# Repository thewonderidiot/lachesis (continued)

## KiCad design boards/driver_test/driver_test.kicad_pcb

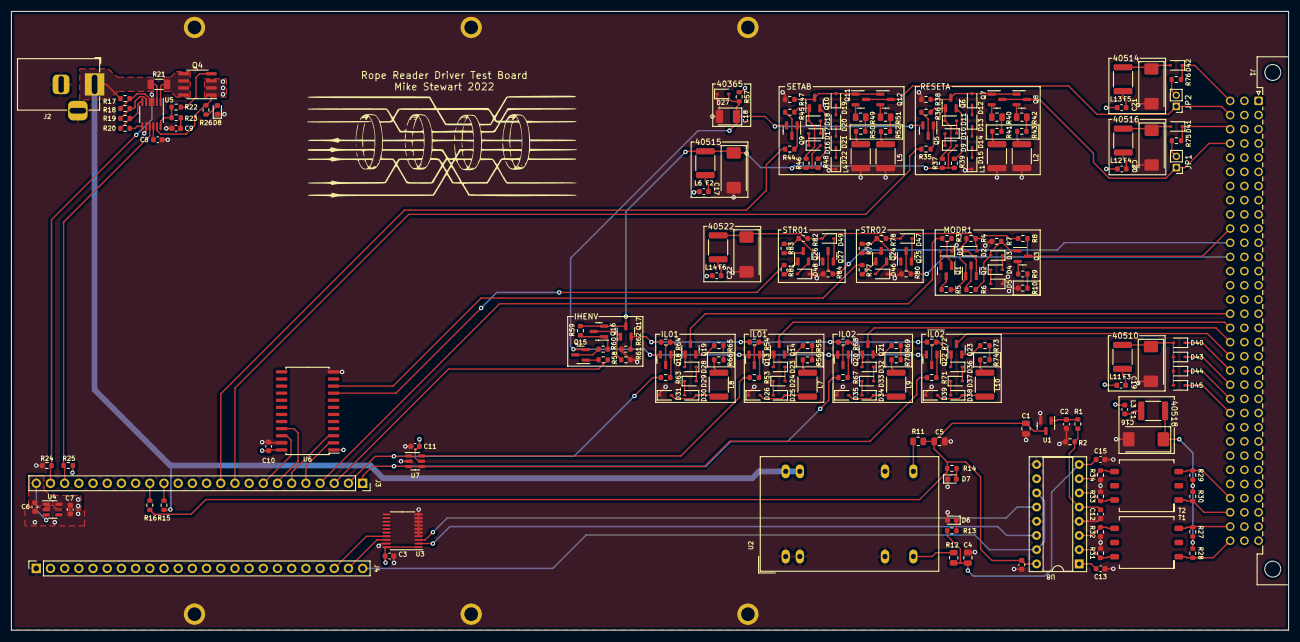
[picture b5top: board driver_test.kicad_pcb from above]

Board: 4 copper layers, 228.6 x 110.7 mm, 224 parts (0 on the bottom side), 175 nets.

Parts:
C1: 4.7uF; C_0805_2012Metric
C2, C6, C7: 1.0uF; C_0603_1608Metric
C3, C10, C11, C14, C15: 0.1uF; C_0603_1608Metric
C4, C5: 1.0uF; C_0805_2012Metric
C8: 0.33uF; C_0603_1608Metric
C9, C12: 10nF; C_0603_1608Metric
C13: 100pF; C_0603_1608Metric
C16, C17, C19, C20, C21, C22: 6.8uF; CP_EIA-7343-31_Kemet-D
C18: 1.0uF; CP_EIA-3528-21_Kemet-B
D1, D2, D3, D4, D5, D9, D10, D11, D12, D13, D14, D15, D16, D17, D18, D19, D20, D21, D22, D23, D24, D25, D26, D27, D28, D29, D30, D31, D32, D33, D34, D35, D36, D37, D38, D39, D40, D41, D42, D43, D44, D45, D46, D47, D48, D49: 1N4148; D_SOD-323
D6: BLUE; LED_0603_1608Metric
D7: TEAL; LED_0603_1608Metric
D8: ORANGE; LED_0603_1608Metric
F1, F2, F3, F4, F5, F6: 250mA; Fuse_0603_1608Metric
H1, H2, H3, H4, H5, H6: MountingHole_Pad; MountingHole_No2_Pad
J1: DIN41612_03x32_C; DIN41612_C_3x32_Male_Horizontal_THT
J2: Barrel_Jack_Switch; BarrelJack_CUI_PJ-002A
J3, J4: Conn_01x24; PinSocket_1x24_P2.54mm_Vertical
JP1, JP2: Jumper_2_Open; PinHeader_1x02_P2.00mm_Vertical
L1, L2, L4, L5: 3.9uH; L_1812_4532Metric
L3, L6, L11, L12, L13, L14: 8.2uH; L_1812_4532Metric
L7, L8, L9, L10: 2.2uH; L_1812_4532Metric
Q1, Q3, Q5, Q7, Q8, Q9, Q11, Q12, Q13, Q14, Q15, Q17, Q18, Q19, Q20, Q21, Q22, Q23, Q24, Q26: MMBT2222; SOT-23
Q2, Q6, Q10, Q16, Q25, Q27: MMBT2907; SOT-23
Q4: IRF7413; SOIC-8_3.9x4.9mm_P1.27mm
R1: 1.27k; R_0603_1608Metric
R2: 249; R_0603_1608Metric
R3, R23, R35, R36, R44, R45, R53, R58, R63, R67, R71, R77, R81: 1k; R_0603_1608Metric
R4, R5, R7, R37, R38, R46, R47, R78, R82: 5.1k; R_0603_1608Metric
R6: 680; R_0603_1608Metric
R8, R57, R80, R84: 3k; R_0603_1608Metric
R9: 8.2; R_0603_1608Metric
R10, R41, R43, R50, R52, R56, R66, R70, R74: NOM; R_0603_1608Metric
R11, R12: 0; R_0805_2012Metric
R13, R14: 430; R_0603_1608Metric
R15: 12k; R_0603_1608Metric
R16: 2.4k; R_0603_1608Metric
R17: 1020k; R_0603_1608Metric
R18: 2.87k; R_0603_1608Metric
R19: 9.76k; R_0603_1608Metric
R20: 54.9k; R_0603_1608Metric
R21: 0.025; R_1206_3216Metric
R22: 10; R_0603_1608Metric
R24, R25: 10k; R_0603_1608Metric
R26: 620; R_0603_1608Metric
R27, R28, R29, R30: 2.7k; R_0603_1608Metric
R31, R32, R33, R34, R59: 470; R_0603_1608Metric
R39, R48: 27; R_0603_1608Metric
R40, R42, R49, R51: 7.5; R_0805_2012Metric
R54, R64, R68, R72: 390; R_0603_1608Metric
R55, R65, R69, R73: 3.9; R_0603_1608Metric
R60, R62, R79, R83: 2k; R_0603_1608Metric
R61: 750; R_0603_1608Metric
R75, R76: 200; R_0603_1608Metric
T1, T2: 1:1; Transformer_Murata_786J
U1: AD1582BRTZ; SOT-23
U2: JTE0624D05; Converter_DCDC_XP_POWER_JTExxxxDxx_THT
U3: 74LVC245; TSSOP-20_4.4x6.5mm_P0.65mm
U4: ADP151-3.3; TSOT-23-5
U5: LTC4231-1; MSOP-12_3x4mm_P0.65mm
U6: 74HC4514; SOIC-24W_7.5x15.4mm_P1.27mm
U7: 74LVC2G04; SOT-23-6
U8: SN7524; DIP-16_W7.62mm_Socket

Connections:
+3V3: C3.2, C7.1, C10.2, C11.1, R25.1, U3.1 (A->B), U3.20 (VCC), U4.5 (VOUT), U6.1 (~LE), U6.24 (VCC), U7.5 (VCC)
+5V: C1.2, C5.1, C14.1, R11.1, R14.1, R16.2, U1.3 (VIN), U8.16 (VCC+)
+14V: F1.2, F2.2, F3.2, F4.2, F5.2, F6.2, Q4.1 (S), Q4.2 (S), Q4.3 (S), R26.1, R57.2, U5.11 (SOURCE)
-5V: C4.2, C15.2, R12.1, R13.1, U8.8 (VCC-)
/40311/4036nA: C18.1, D27.2 (A), Q5.2 (E), Q9.2 (E), Q13.2 (E), Q15.2 (E), Q18.2 (E), Q20.2 (E), Q22.2 (E), R57.1
/40312/IN: R53.2, U7.6
/40314/IN: R71.2, U7.4
/40331/IN: J3.3, R58.2
/40331A: Q17.2 (E), R54.1, R62.1, R64.1, R68.1, R72.1
/40601a/SEn: R81.2, U6.9 (Y1)
/40601b/SEn: R77.2, U6.10 (Y2)
/BPLIZ1: C17.1, D9.2 (A), D16.2 (A), L6.2, Q16.2 (E), Q17.3 (C), R37.1, R39.1, R46.1, R48.1, R59.1
/BPLMX1: C19.1, D40.2 (A), D43.2 (A), D44.2 (A), D45.2 (A), L11.2
/BPLMX3: C21.1, D42.2 (A), L13.2
/BPLMY3: C20.1, D41.2 (A), L12.2
/BPLSWX: C16.1, L3.2, R27.2, R28.1, R29.2, R30.1
/BPLSWZ: C22.1, D2.2 (A), D47.2 (A), D49.2 (A), L14.2, R4.1, R8.1, R78.1, R82.1
/FPGA and Power/5V_FPGA: C6.2, J3.24, U4.1 (VIN), U4.3 (EN)
/FPGA and Power/14V_IN: J2.1, R15.2, R17.2, R21.1, U2.22 (VIN+), U2.23 (VIN+), U5.2 (IN)
/FPGA and Power/14V_SENSE: Q4.5 (D), Q4.6 (D), Q4.7 (D), Q4.8 (D), R21.2, U5.1 (SENSE)
/FPGA and Power/ADC_5V: J3.16, R16.1
/FPGA and Power/ADC_14V: J3.15, R15.1
/FPGA and Power/EN_14V: J3.23, R24.1, U5.3 (~SHDN)
/FPGA and Power/IL1: J3.2, R63.2, U7.1
/FPGA and Power/IL2: J3.1, R67.2, U7.3
/FPGA and Power/PG_14V: J3.22, R25.2, U5.9 (STATUS)
/FPGA and Power/RESET1: J3.10, R35.2
/FPGA and Power/ROPER: J3.4, R3.2
/FPGA and Power/SA1: U3.2 (A0), U8.14
/FPGA and Power/SA2: U3.3 (A1), U8.12
/FPGA and Power/SAF1: J4.23, U3.18 (B0)
/FPGA and Power/SAF2: J4.22, U3.17 (B1)
/FPGA and Power/SBF: J4.24, U8.11, U8.15
/FPGA and Power/SET1: J3.11, R44.2
/FPGA and Power/STRA0: J3.5, U6.2 (A0)
/FPGA and Power/STRA1: J3.6, U6.3 (A1)
/FPGA and Power/STRA2: J3.7, U6.21 (A2)
/FPGA and Power/STRA3: J3.8, U6.22 (A3)
/GAR1: J1.c31, R27.1, T1.3 (P2)
/GAR2: J1.c29, R29.1, T2.3 (P2)
/GBR1: J1.c32, R28.2, T1.1
/GBR2: J1.c30, R30.2, T2.1
/MODR1: J1.c10, Q3.3 (C), R8.2
/RCD1: D43.1 (K), J1.c21
/RCD2: D45.1 (K), J1.c23
/RFD1: D40.1 (K), J1.c20
/RFD2: D44.1 (K), J1.c22
/RPR: Q1.3 (C), R5.2
/RSTRN1: D41.1 (K), J1.c3, R75.2
/SETRN1: D42.1 (K), J1.c1, R76.2
/STR1: J1.c11, Q27.3 (C), R84.1
/STR2: J1.c12, Q25.3 (C), R80.1
/VREF: C12.2, R1.2, R2.1, U8.5 (+)
/XCN1: J1.c17, Q14.3 (C)
/XCN2: J1.c19, Q23.3 (C)
/XFN1: J1.c16, Q19.3 (C)
/XFN2: J1.c18, Q21.3 (C)
/XRST1: J1.c4, JP1.1 (A), Q7.3 (C), Q8.3 (C)
/XSET1: J1.c2, JP2.1 (A), Q11.3 (C), Q12.3 (C)
GND: C1.1, C2.2, C3.1, C4.1, C5.2, C6.1, C7.2, C8.2, C9.2, C10.1, C11.2, C12.1, C13.1, C14.2, C15.1, C16.2, C17.2, C18.2, C19.2, C20.2, C21.2, C22.2, D1.1 (K), D5.1 (K), D6.2 (A), D7.1 (K), D8.1 (K), D15.1 (K), D22.1 (K), D26.1 (K), D27.1 (K), D31.1 (K), D35.1 (K), D39.1 (K), D46.1 (K), D48.1 (K), H1.1, H2.1, H3.1, H4.1, H5.1, H6.1, J2.2, J2.3, J4.1, L1.2, L2.2, L4.2, L5.2, R2.2, R7.2, R10.2, R24.2, R31.2, R32.1, R33.2, R34.1, R38.2, R47.2, R61.2, R62.2, R80.2, R84.2, U1.2 (GND), U2.2 (VIN-), U2.3 (VIN-), U2.9 (COM), U2.16 (COM), U3.4 (A2), U3.5 (A3), U3.6 (A4), U3.7 (A5), U3.8 (A6), U3.9 (A7), U3.10 (GND), U3.19 (CE), U4.2 (GND), U5.8 (GND), U6.12 (GND), U6.23 (~E), U7.2 (GND), U8.4 (-), U8.9 (GND), U8.13 (GND)
unnamed: C2.1, R1.1, U1.1 (VOUT)
unnamed: C8.1, U5.10 (TIMER)
unnamed: C9.1, R23.1
unnamed: C13.2, U8.1 (CEXT)
unnamed: D1.2 (A), Q1.2 (E)
unnamed: D2.1 (K), Q2.2 (E)
unnamed: D3.1 (K), D4.2 (A)
unnamed: D3.2 (A), Q3.1 (B), R6.2, R7.1
unnamed: D4.1 (K), D5.2 (A)
unnamed: D6.1 (K), R13.2
unnamed: D7.2 (A), R14.2
unnamed: D8.2 (A), R26.2
unnamed: D10.1 (K), D11.2 (A)
unnamed: D9.1 (K), D10.2 (A)
unnamed: D11.1 (K), Q6.1 (B), R36.1, R37.2
unnamed: D12.1 (K), D13.2 (A)
unnamed: D12.2 (A), Q6.3 (C), Q7.1 (B), Q8.1 (B), R38.1
unnamed: D13.1 (K), D14.2 (A)
unnamed: D14.1 (K), D15.2 (A)
unnamed: D16.1 (K), D17.2 (A)
unnamed: D17.1 (K), D18.2 (A)
unnamed: D18.1 (K), Q10.1 (B), R45.1, R46.2
unnamed: D19.1 (K), D20.2 (A)
unnamed: D19.2 (A), Q10.3 (C), Q11.1 (B), Q12.1 (B), R47.1
unnamed: D20.1 (K), D21.2 (A)
unnamed: D21.1 (K), D22.2 (A)
unnamed: D23.1 (K), D24.2 (A)
unnamed: D23.2 (A), Q13.3 (C), Q14.1 (B), R54.2
unnamed: D24.1 (K), D25.2 (A)
unnamed: D25.1 (K), D26.2 (A), L7.2
unnamed: D28.1 (K), D29.2 (A)
unnamed: D28.2 (A), Q18.3 (C), Q19.1 (B), R64.2
unnamed: D29.1 (K), D30.2 (A)
unnamed: D30.1 (K), D31.2 (A), L8.2
unnamed: D32.1 (K), D33.2 (A)
unnamed: D32.2 (A), Q20.3 (C), Q21.1 (B), R68.2
unnamed: D33.1 (K), D34.2 (A)
unnamed: D34.1 (K), D35.2 (A), L9.2
unnamed: D36.1 (K), D37.2 (A)
unnamed: D36.2 (A), Q22.3 (C), Q23.1 (B), R72.2
unnamed: D37.1 (K), D38.2 (A)
unnamed: D38.1 (K), D39.2 (A), L10.2
unnamed: D46.2 (A), Q24.2 (E)
unnamed: D47.1 (K), Q25.2 (E)
unnamed: D48.2 (A), Q26.2 (E)
unnamed: D49.1 (K), Q27.2 (E)
unnamed: F1.1, L3.1
unnamed: F2.1, L6.1
unnamed: F3.1, L11.1
unnamed: F4.1, L12.1
unnamed: F5.1, L13.1
unnamed: F6.1, L14.1
unnamed: JP1.2 (B), R75.1
unnamed: JP2.2 (B), R76.1
unnamed: L1.1, R41.2
unnamed: L2.1, R43.2
unnamed: L4.1, R50.2
unnamed: L5.1, R52.2
unnamed: L7.1, R56.2
unnamed: L8.1, R66.2
unnamed: L9.1, R70.2
unnamed: L10.1, R74.2
unnamed: Q1.1 (B), R3.1
unnamed: Q2.1 (B), R4.2, R5.1
unnamed: Q2.3 (C), R6.1
unnamed: Q3.2 (E), R9.1
unnamed: Q4.4 (G), R22.1
unnamed: Q5.1 (B), R35.1
unnamed: Q5.3 (C), R36.2
unnamed: Q6.2 (E), R39.2
unnamed: Q7.2 (E), R40.1
unnamed: Q8.2 (E), R42.1
unnamed: Q9.1 (B), R44.1
unnamed: Q9.3 (C), R45.2
unnamed: Q10.2 (E), R48.2
unnamed: Q11.2 (E), R49.1
unnamed: Q12.2 (E), R51.1
unnamed: Q13.1 (B), R53.1
unnamed: Q14.2 (E), R55.1
unnamed: Q15.1 (B), R58.1
unnamed: Q15.3 (C), R60.2
unnamed: Q16.1 (B), R59.2, R60.1
unnamed: Q16.3 (C), Q17.1 (B), R61.1
unnamed: Q18.1 (B), R63.1
unnamed: Q19.2 (E), R65.1
unnamed: Q20.1 (B), R67.1
unnamed: Q21.2 (E), R69.1
unnamed: Q22.1 (B), R71.1
unnamed: Q23.2 (E), R73.1
unnamed: Q24.1 (B), R77.1
unnamed: Q24.3 (C), R79.2
unnamed: Q25.1 (B), R78.2, R79.1
unnamed: Q26.1 (B), R81.1
unnamed: Q26.3 (C), R83.2
unnamed: Q27.1 (B), R82.2, R83.1
unnamed: R9.2, R10.1
unnamed: R11.2, U2.14 (VOUT+)
unnamed: R12.2, U2.11 (VOUT-)
unnamed: R17.1, R18.2, U5.4 (UVL)
unnamed: R18.1, R19.2, U5.5 (UVH)
unnamed: R19.1, R20.2, U5.6 (OV)
unnamed: R20.1, U5.7 (GNDSW)
unnamed: R22.2, R23.2, U5.12 (GATE)
unnamed: R31.1, T1.4 (S2), U8.2
unnamed: R32.2, T1.6 (S1), U8.3
unnamed: R33.1, T2.4 (S2), U8.6
unnamed: R34.2, T2.6 (S1), U8.7
unnamed: R40.2, R41.1
unnamed: R42.2, R43.1
unnamed: R49.2, R50.1
unnamed: R51.2, R52.1
unnamed: R55.2, R56.1
unnamed: R65.2, R66.1
unnamed: R69.2, R70.1
unnamed: R73.2, R74.1

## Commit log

2021-10-18 First batch of relevant documentation
2021-10-26 Initial schematicery
2021-10-26 Initial interface board
2021-10-31 Added a sheet containing all of the required current drivers to the interface board
2021-10-31 Driver board: added strand selection and return circuits
2021-11-02 Driver board: added a preliminary sheet for the FPGA connector and interfacing circuitry
2021-11-03 Driver boards: filled out all of the FPGA connections. Power circuits to still be defined.
2021-11-08 Completely overhauled rope driver circuitry to much, much more closely resemble the original.
2021-11-09 Driver board: a bit more schematic work and some initial footprint selections
2021-11-11 Driver board: finished first rough draft schematic. Lots of placeholders, but at least every place is held.
2021-11-14 Driver board: fleshed out the hotswap controller, tweaked some resistors, and added some bypass caps
2021-11-16 Driver board: significant cleanup. Moved sense amp pairs into a subsheet, split tuning resistors into two globally, pushed input circuits into their corresponding sheets.
2021-11-18 Backplane board: new name, and initial integration of DIN-41612 3x32 C connector
2021-11-18 Driver board: integrated DIN 41612 backplane connector, and made a dedicated parity inhibit sheet with a different set resistor value.
2021-12-01 Driver: incorporated some power LEDs
2021-12-11 FPGA: Initial, barebones microblaze project
2021-12-12 Initial firmwarey
2021-12-12 Added LED footprints and ignored bitstream files
2021-12-13 Firmware: initial framework for interrupt-driven UART comms. Circularly-buffered variable-length slipped transmission works; reception next.
2021-12-13 Firmware: largely fleshed out UART command reception and decoding
2021-12-14 FPGA/FW: Added a watchdog timer and made a simple library for it
2022-01-15 Driver board: largely fleshed out part selection
2022-01-23 Driver: updated to KiCad 6.0
2022-02-13 Added a simplified test driver board, for proof-of-concept testing with a 2-bit, 2-strand, 2-core rope
2022-02-14 Driver: Added a 5V->3.3V LDO to replace the reversed cmod header, added jumpers for the 200R parallel returns, and renamed subcircuit ports to avoid unexpected ground connections.
2022-02-15 Driver: some high-level board rearrangement and addition of 3d models
2022-02-24 Driver test: completed much of the preliminary layout.
2022-03-02 Added the beginnings of a rope module database
2022-03-03 Filled out rope table up through Luminary 69 (deck 281)
2022-03-08 Driver test: finished up board layout
2022-03-08 Gerber files for v1 of the driver test board
2022-03-08 Driver test: some updates to component values based on new documentation
2022-03-26 FPGA: Regenerated things because Vivado saved some really weird stuff. Firmware is broken.
2022-03-27 FPGA: Fleshed out FPGA project, and brought UART and ADC cores online
2022-03-27 Firmware: incorporated sys library for timing/ADC, and regenerated for different vitis version
2022-03-27 GUI: Very rough first cut that can interface with the serial port. Much more to go.
2022-03-27 Added a simple test rope board to implement a test 2-bit, 2-strand, 2-core rope compatible with the driver test board
2022-03-27 Driver test: some minor component value changes
2022-03-30 Firmware: large refactor for mixed-length commands.
2022-03-30 GUI: Completed the timing window and updated the USB interface to match the new protocol
2022-03-30 FPGA: Added preliminary rope driver IP
2022-04-02 GUI: Added BPLSSW enable to the main window (to be prettified later)
2022-04-02 Firmware: Incorporated rope driver functionality, and added basic status reporting and enable/disable commands
2022-04-02 FPGA: fleshed out IP driver and changed some register read behavior
2022-04-03 Driver test: updated schematic with new coarse tuning resistance values for all 3 current driver types
2022-04-03 Firmware: added commands to individually pulse all circuits
2022-04-03 GUI: Added a manual controls window for pulsing circuits and kicking off single address read cycles
2022-04-06 Driver test: dropped BPLSSW LED brightness by bumping its resistor up to 1k
2022-04-06 FPGA: Corrected polarity of inhibit driver enables
2022-04-06 Firmware: added a command to read an entire strand, and a state machine to sequence it
2022-04-06 GUI: Added temporary main window widgets for strand data display
2022-05-22 Backplane-BLK2: Footprints laid out and preliminary sense routing
2022-05-22 Boards: added better inductor and diode footprints based on test board learning
2022-06-02 Added STEP files and mechanical drawings for the chassis
2022-06-02 Driver: incorporated most changes from the test board, and began layout
2022-06-07 Driver: laid out most of the subcircuits
2022-06-09 Filled out rope module database up through Apollo 13
2022-06-09 Completed adding all Block II ropes to the database (except for DIGFLY)
2022-06-17 Driver: positioned the sense amps and laid out all of the sense wires
2022-06-19 Driver: lightly reorganized FPGA wiring to make it easier to change in the future, and fixed sense amp mapping
2022-06-20 Driver: progress on subcircuit layout and overall placement
2022-06-21 Driver: 3.3V section is now laid out, contained entirely beneath the FPGA daughter board
2022-06-29 Backplane: completed preliminary layout
2022-06-30 Backplane: a little bit of schematic and silkscreen cleanup
2022-06-30 Driver: incorporated completed backplane pinout and did a little bit more routing on the board
2022-07-03 Driver: Completed preliminary placement on the top layer. <200 unwired nets to go.
2022-07-04 Driver: lots of silkscreen work and fine-tuning of top layer placement
2022-07-04 Backplane: added a fancier rope graphic
2022-07-04 Driver: more work fine-tuning and fancy-fying the top layout. Only sense amp power and rope return circuits need sprucing up now.
2022-07-05 Driver: completed placement on both sides, barring final adjustments
2022-07-06 Driver: completed routing all power nets; 123 nets left to go
2022-07-10 Driver: a bit more routing work. May revisit 3.3V logic placement to ease contention around the FPGA
2022-07-11 Driver: almost totally rearranged 3.3V logic section. The ratsnest is now significantly detangled, and the FPGA routing is almost done. 89 nets left.
2022-07-12 Driver: routed 5V sense amplifier signals and remaining circuit enables. All 63 remaining connections are to the backplane connector.
2022-07-18 Backplane: added names for unconnected rope module pins for completeness
2022-07-18 Driver: routed a few more signals and annotated net equivalent names for the rope connector
2022-07-23 Driver: completed first pass layout. All nets routed, 0 DRC errors.
2022-07-24 Driver: added ground pours to all layers and corrected orientations of all refdes
2022-07-30 Backplane: fleshed out silkscreen and finalized first revision
2022-08-07 GUI: Lots of fleshing out. Most things aside from saving the dump are in place
2022-08-08 Driver: minor schematic cleanup and populated all of the BOM except for resistors
2022-08-08 Driver: filled out the rest of the BOM, except for defaults for nominal resistances
2022-08-09 Driver: completed the BOM and added some reference dimensions to the board layout
2022-08-09 Driver: updated board from schematic to pull over MPN information for BOM
2022-08-12 FPGA: Updated for full rope driver board. Untested, and firmware still needs to be updated.
2022-08-12 Driver: added FPGA ball numbers to the schematic
2022-08-12 Firmware: updated hardware spec and implemented full versions of individual circuit exercising commands
2022-08-13 GUI: Implemented basic state machine for reading full ropes
2022-08-13 GUI: Fixed FF banksum determination
2022-08-13 GUI: Implemented rope dump saving
2022-08-13 Driver: commited formerly uncommitted silkscreen art
2022-08-14 Driver: corrected reference divider resistor and added diode direction symbols to the silkscreen
2022-08-14 Driver: touched up diode silkscreen a bit
2022-08-20 Driver: increased pours clearance to 20 mils, removed ground pours from outer layers, adjusted thermal reliefs, and adjusted some plane outlines
2022-08-20 Driver: a bit more pour cleanup
2022-09-27 Block 1: added preliminary backplane board
2022-09-29 Block I: finished up the first pass on the backplane
2022-10-09 GUI: Cleaned up manual address/word display and added a delay for PGOOD checking
2022-10-09 Firmware: added a temporary artifical delay to appease the hotswap controller
2022-10-10 FPGA: Corrected parity inhibit calculation to cover the bottom 8 (instead of 7) bits of the address
2022-10-10 Added first two successful module dumps
2022-10-15 GUI: Removed redundant second read for manual addresses
2022-10-15 FPGA: Added previously untracked component.xml file
2022-10-20 GUI: Initial updates for Block I version, with new separate launcher script. Disassembly is not yet updated.
2022-10-20 Added dump of Sunrise 69 module B22
2022-10-20 Firmware: added support for Block I addressing via new Block I-specific commands
2022-10-20 Added all Block I rope modules to the rope database (sans banksums)
2022-10-22 GUI: Finished up Block I changes
2022-10-22 Added bugger words for Solarium 55 to the rope database
2022-10-26 Added checksums for some Aurora and Sundial ropes, based on new dumps
2022-10-26 Added a variety of new module dumps
2022-11-16 Added dump of Aurora 88 module B2, p/n 2003972-091
2023-09-16 Firmware: add support for sensing Block I ropes during both set and reset, in case of multiple diode failure
2023-09-16 Rope DB: added now-known buggers for Corona 261
2023-09-16 Added dumps of all six flown Corona 261 modules
2023-09-16 Added dumps of 5 of the 6 Solarium 55 ropes flown on Apollo 4
2023-09-16 Added dumps of two modules of Colossus 236/237
2023-12-08 Rough initial code for running a bad bit capture with a picoscope
2023-12-10 Add 5 raw dumps of Sunrise modules
2024-04-25 Add dumps of all six modules of Skylark 48
2024-04-25 Update GUI to PySide6
2024-04-28 Rework USB interface to enable unplugging and replugging without restarting GUI
2024-04-28 Interface with Qt through qtpy for better portability
2024-07-05 Add dedicated window for data capture with picoscope
2024-07-06 Allow scope capture to adjust timing and strobe during both set and reset
2026-02-19 Add ALL strands option to the scope window
2026-02-19 Initial README.md work
2026-03-01 Add dumps of all six modules of Comanche 67
2026-03-01 Mark a few known Block I ropes as definitely Sunspot
